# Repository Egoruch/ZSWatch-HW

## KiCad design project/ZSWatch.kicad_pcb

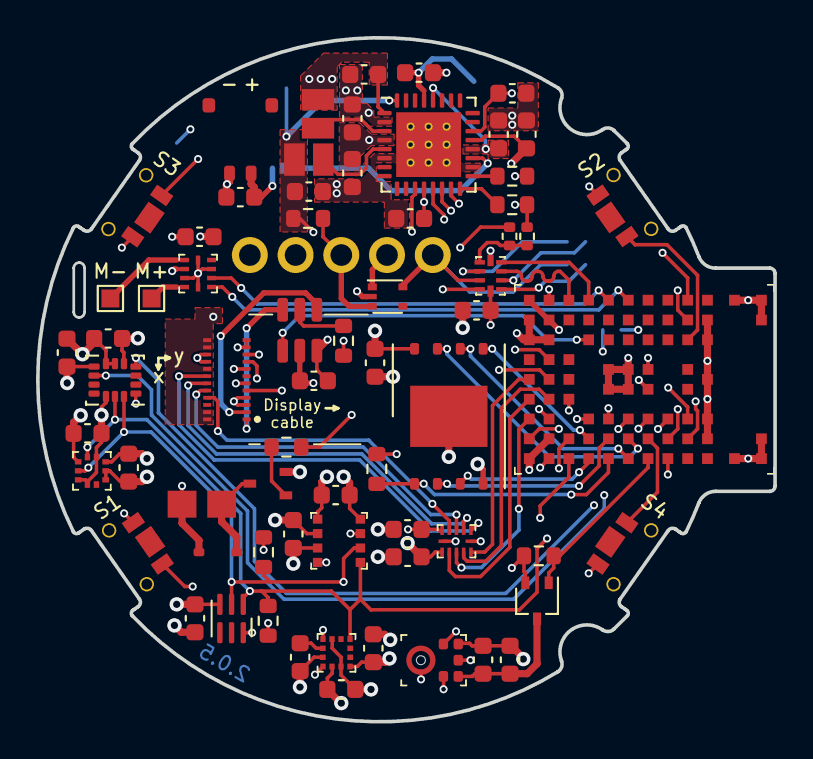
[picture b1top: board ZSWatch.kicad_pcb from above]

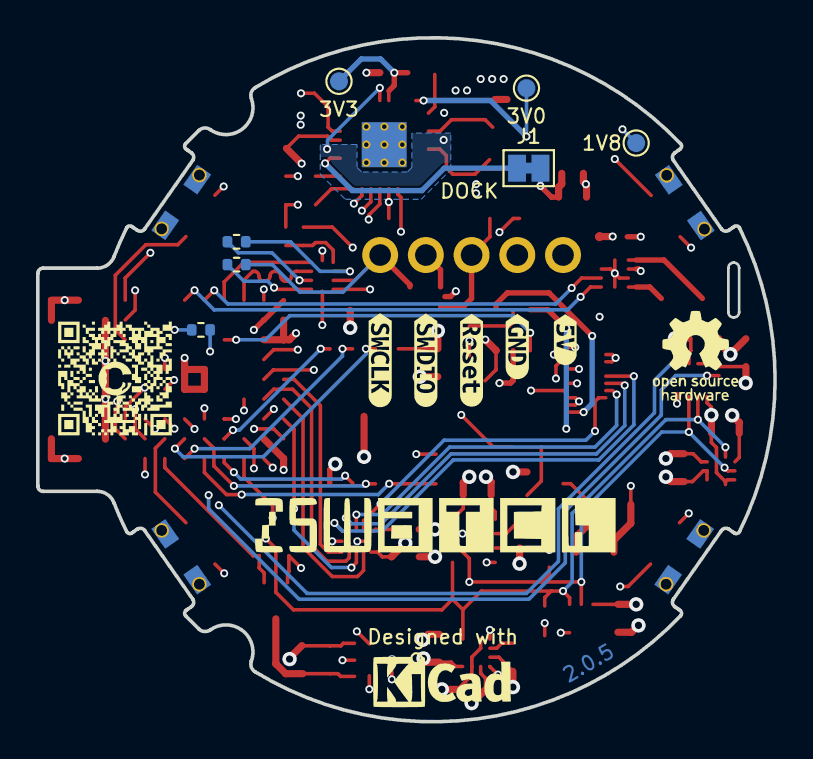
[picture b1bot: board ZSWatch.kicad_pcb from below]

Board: 4 copper layers, 41.0 x 38.0 mm, 80 parts (13 on the bottom side), 69 nets.

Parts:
BZ1: Buzzer; CMT-322-65-SMT-TR
C1, C10, C21, C23: 1u; C_0603_1608Metric
C2, C11, C12, C13, C14, C15, C18, C19, C20, C22, C25, C26, C27, C28: 100n; C_0603_1608Metric
C3: 2u2; C_0603_1608Metric
C4, C5, C6, C7, C8, C9, C17: 10u; C_0603_1608Metric
C16: 220n; C_0603_1608Metric
C24: 200p; C_0603_1608Metric
D1: BAS316; D_SOD-323
IC1: nPM1300-QEXX; QFN-32-1EP_5x5mm_P0.5mm_EP3.6x3.6mm_ThermalVias
IC2: APDS-9306-065; Broadcom_DFN-6_2x2mm_P0.65mm
IC3: BMI270; LGA-14_3x2.5mm_P0.5mm_LayoutBorder3x4y
IC4: BMP581; Bosch_LGA-10_2x2mm_P0.5mm_ClockwisePinNumbering
IC5: LIS2MDLTR; LGA-12_2x2mm_P0.5mm
IC6: BME688; Bosch_LGA-8_3x3mm_P0.8mm_ClockwisePinNumbering
IC7: ESDALC6V1W5; SOT-665
IC8: FAN5622SX; TSOT-23-6
IC9: S25FS512SAGNFI010; WSON-8-1EP_8x6mm_P1.27mm_EP3.4x4.3mm
IC10: TS3USB221A; UQFN-10_1.55x2.05mm_P0.5mm
IC11: NTS0104GU12; XQFN-12-1.7x2mm_P0.4mm
IC12: DRV2603RUNT; WQFN-10_2x2mm_P0.5mm
J1: SolderJumper-2_P1.3mm_Bridged_Pad1.0x1.5mm
L1, L2: 2u2; L_0806_2016
M1: NORA-B106
MK1: SPH0645LM4H-B; SPH0645LM4H-6_3.5x2.65mm
Q1: BC817W; SOT-323_SC-70
Q3: DMG1013UW-7; SOT-323_SC-70
R1: 47k; R_0603_1608Metric
R2, R14: 150k; R_0603_1608Metric
R3: 12k; R_0603_1608Metric
R4, R8: 100k; R_0603_1608Metric
R5, R6: 4k7; R_0603_1608Metric
R7: 180R; R_0603_1608Metric
R9, R10, R11, R12, R13: 0R; R_0402_1005Metric
S1, S2, S3, S4: TL6340AF160Q; TL6340AF160Q_Modified
TP1: 3V3; TestPoint_Pad_D1.0mm
TP2: 1V8; TestPoint_Pad_D1.0mm
TP3: 3V0; TestPoint_Pad_D1.0mm
X1: BATTERY; 78171-0002
X2: DOCK; RD90_LZH0230529-004_DJ-5PIN_PH2_54
X3: GC9A01A_CST816S; ER-CON0.4-24P
X4: M+; TestPoint_Pad_1.0x1.0mm
X5: M-; TestPoint_Pad_1.0x1.0mm
kibuzzard-656642B5: G***; kibuzzard-656642B5
kibuzzard-656642E4: G***; kibuzzard-656642E4
kibuzzard-65664307: G***; kibuzzard-65664307
kibuzzard-65664337: G***; kibuzzard-65664337
kibuzzard-65664342: G***; kibuzzard-65664342

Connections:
+1V8: C2.1, C7.1, C11.1, C12.1, C13.2, C14.2, C15.1, C17.1, C18.1, C19.1, C20.2, C22.1, C26.1, IC1.1 (VOUT1), IC1.12 (VDDIO), IC2.3 (VDD), IC3.5 (VDDIO), IC3.8 (VDD), IC3.12 (CSB), IC4.1 (VDDIO), IC4.5 (SDO), IC4.6 (CSB), IC4.10 (VDD), IC5.3 (CS), IC5.9 (VDD), IC5.10 (VDDIO), IC6.2 (CSB), IC6.6 (VDDIO), IC6.8 (VDD), IC9.8 (VCC), IC11.1 (VCCA), L2.1, M1.A7 (VDD), M1.A8 (VDDH), M1.B7 (VDD), Q3.2 (S), R4.1, R5.2, R6.2, R14.2, TP2.1, X3.11 (VDDIO), X3.12 (VDDIO)
+3V0: BZ1.1 (-), C5.1, C25.1, D1.1 (K), IC1.32 (VOUT2), IC10.10 (VDD), L1.1, R8.1, R10.2, TP3.1
/MCU/BMI270-INT1: IC3.4 (INT1), M1.G5 (P1.08)
/MCU/BMI270-INT2: IC3.9 (INT2), M1.G4 (P1.04)
/MCU/LIS2MDL_INT: IC5.7 (INT/DRDY), M1.H1 (P0.24)
/MCU/MIC_BCLK: M1.G3 (P0.25/AIN4), MK1.4 (BCLK)
/MCU/MIC_DATA: M1.F3 (P0.19), MK1.6 (DATA)
/MCU/MIC_EN: M1.G1 (P1.06), Q3.1 (G), R14.1
/MCU/MIC_SEL: M1.E3 (P0.21), MK1.2 (SEL)
/MCU/PMIC-INT: IC1.11 (GPIO4), M1.J8 (P0.28/AIN7)
/MCU/SENSOR-SCL: IC1.14 (SCL), IC2.1 (SCL), IC3.13 (SCK), IC4.2 (SCK), IC5.1 (SCL/SPC), IC6.4 (SCK), M1.D3 (P0.07/AIN3), R5.1
/MCU/SENSOR-SDA: IC1.13 (SDA), IC2.2 (SDA), IC3.14 (SDI), IC4.4 (SDI), IC5.4 (SDA/SDI/SDO), IC6.3 (SDI), M1.C1 (P0.10/TRACEDATA[1]), R6.1
/MCU/VBAT: C3.1, C28.1, IC12.7 (VDD), J1.1 (A), X1.1
/MCU/VBUS-MCU: C10.1, IC1.22 (VBUSOUT), M1.B9 (VBUS)
/MCU/VDD-Display: C8.1, C21.2, C27.1, IC1.29 (LSOUT1/VOUTLDO1), IC8.3 (VIN), IC11.11 (VCCB), TP1.1, X3.13 (VDD), X3.14 (VDD), X3.17 (CTP-VDD), X3.23 (LEDA2), X3.24 (LEDA1)
BTN_1: M1.H3 (P0.27/AIN6), S1.1
BTN_2: M1.J7 (P1.10), S2.2
BTN_3: IC1.15 (SHPHLD), M1.J9 (P0.31), S3.2
BTN_4: M1.G2 (P0.26/AIN5), S4.1
BUZZER: M1.B6 (P0.01/XL2), R7.1
D+/SWDCLK: IC7.5 (I/04), IC10.8 (D+), R12.2, X2.1
D-/SWDIO: IC7.1 (I/01), IC10.7 (D-), R11.2, X2.2
DISPLAY_BLK: IC8.1 (CTRL), M1.D7 (P0.23)
DISPLAY_CLK: M1.B1 (P0.08/TRACEDATA[3]), X3.8 (SCL)
DISPLAY_CS: M1.A2 (P0.12/TRACECLK), X3.9 (CS)
DISPLAY_DATA: M1.C2 (P0.09/TRACEDATA[2]), X3.6 (SDI/SDA)
DISPLAY_DC: M1.B3 (P0.11/TRACEDATA[0]), X3.5 (RS/DC)
DISPLAY_EN: IC11.12 (OE), M1.C4 (P1.01)
DISPLAY_RST: M1.B5 (P0.03/NFC2), X3.10 (RESET)
DRV_VIB_EN: IC12.1 (EN), M1.F9 (P1.15)
DRV_VIB_PWM: IC12.2 (PWM), M1.E9 (P1.05)
GND: C1.2, C2.2, C3.2, C4.2, C5.2, C6.2, C7.2, C8.2, C9.2, C10.2, C11.2, C12.2, C13.1, C14.1, C15.2, C16.2, C17.2, C18.2, C19.2, C20.1, C21.1, C22.2, C23.1, C24.1, C25.2, C26.2, C27.2, C28.2, IC1.2 (PVSS1), IC1.6 (PVSS2), IC1.18 (NTC), IC1.33 (AVSS), IC2.6 (GND), IC3.1 (SDO), IC3.6 (GND), IC3.7 (GND), IC4.3 (GND), IC4.8 (GND), IC4.9 (GND), IC5.6 (GND), IC5.8 (GND), IC6.1 (GND), IC6.5 (SDO), IC6.7 (GND), IC7.2 (GND), IC8.2 (GND), IC9.4 (GND), IC9.9 (EP), IC10.5 (GND), IC11.6 (GND), IC12.3 (LRA/~ERM), IC12.5 (GND), IC12.8 (GND), IC12.10 (GND), M1.A1 (GND), M1.A9 (GND), M1.B2 (GND), M1.B8 (GND), M1.E4 (GND), M1.E5 (GND), M1.F4 (GND), M1.F5 (GND), M1.K2 (GND), M1.K3 (GND), M1.K5 (GND), M1.K7 (GND), M1.K8 (GND), M1.L1 (GND), M1.L9 (GND), M1.M1 (GND), M1.M2 (GND), M1.M8 (GND), M1.M9 (GND), MK1.1 (WS), MK1.3 (GND), Q1.2 (E), R1.1, R2.1, R3.1, R13.2, S1.2, S2.1, S3.1, S4.2, X1.2, X2.4, X3.3 (GND), X3.4 (GND), X3.15 (GND), X3.16 (GND)
LEDK1: IC8.6 (LED1), X3.1 (LEDK-1)
LEDK2: IC8.4 (LED2), X3.2 (LEDK-2)
MCU_D_N: IC10.4 (2D-), M1.D9 (D-)
MCU_D_P: IC10.3 (2D+), M1.C9 (D+)
MCU_SWDCLK: IC10.1 (1D+), M1.J2 (SWDCLK), R12.1
MCU_SWDIO: IC10.2 (1D-), M1.H2 (SWDIO), R11.1
unnamed: BZ1.2 (+), D1.2 (A), Q1.3 (C)
unnamed: IC1.3 (SW1), L2.2
unnamed: IC1.5 (SW2), L1.2
unnamed: IC1.19 (VBAT), J1.2 (B)
unnamed: IC1.17 (VSET1), R1.2
unnamed: IC1.16 (VSET2), R2.2
unnamed: C16.1, IC5.5 (C1)
unnamed: IC8.5 (ISET), R3.2
unnamed: IC10.6 (~OE), R10.1, R13.1
unnamed: IC11.10 (B1), X3.21 (CTP-INT)
unnamed: IC11.9 (B2), X3.20 (CTP-SCL)
unnamed: IC11.8 (B3), X3.19 (CTP-SDA)
unnamed: IC11.7 (B4), X3.18 (CTP-RST)
unnamed: IC12.9 (OUT+), X4.1
unnamed: IC12.6 (OUT-), X5.1
unnamed: C23.2, C24.2, MK1.5 (VDD), Q3.3 (D)
unnamed: Q1.1 (B), R7.2
QSPI_CLK: IC9.6 (SCK), M1.F1 (P0.17/QSPI_CLK)
QSPI_CS: IC9.1 (~CS), M1.E1 (P0.18/QSPI_CS), R4.2
QSPI_IO0: IC9.5 (SI(I/O0)), M1.D2 (P0.13/QSPI[0])
QSPI_IO1: IC9.2 (SO(I/O1)), M1.E2 (P0.14/QSPI[1])
QSPI_IO2: IC9.3 (~WP(I/O2)), M1.D1 (P0.15/QSPI[2])
QSPI_IO3: IC9.7 (~HOLD(I/O3)), M1.F2 (P0.16/QSPI[3])
RESETn: M1.J3 (~RESET), R9.2
SEL_SWD: IC7.3 (I/02), IC10.9 (S), R8.2, R9.1, X2.3
TOUCH_INT: IC11.2 (A1), M1.A4 (P1.00)
TOUCH_RST: IC11.5 (A4), M1.A5 (P0.20)
TOUCH_SCL: IC11.3 (A2), M1.A3 (P1.03/I2C)
TOUCH_SDA: IC11.4 (A3), M1.B4 (P1.02/I2C)
VBUS: C1.1, IC1.21 (VBUS), X2.5
VSYS: C4.1, C6.1, C9.1, IC1.4 (PVDD), IC1.20 (VSYS), IC1.28 (LSIN1/VINLDO1)

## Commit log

2024-01-10 test: sch changes
2024-01-10 test: fron another repo
2024-01-10 test: sch fabout
